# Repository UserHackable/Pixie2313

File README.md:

## Pixie 2313 / 4313

A very bare minimum breakout for an ATtiny2313 to provide the AVR ICSP programming header to the micro controller. 

## Pixie2313 

### Board dimensions

* (140000, 80000) original units
* (1.4000, 0.8000) inches
* (35.5600, 20.3200) mm

| Front | Back |
| --- | --- |
|  |  |

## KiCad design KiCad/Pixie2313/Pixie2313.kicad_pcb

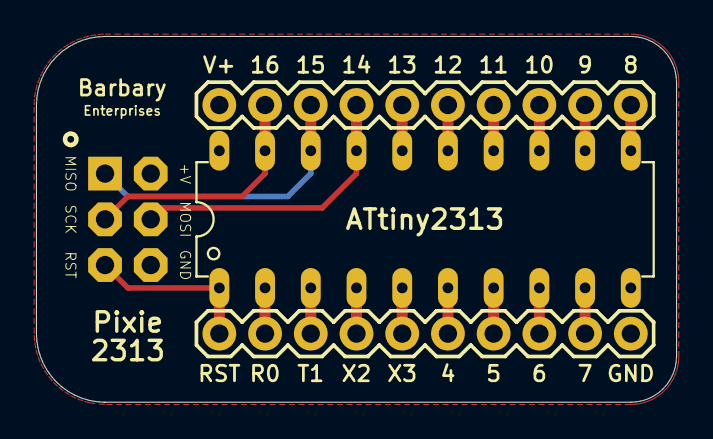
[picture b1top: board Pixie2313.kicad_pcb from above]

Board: 2 copper layers, 35.6 x 20.3 mm, 4 parts (0 on the bottom side), 20 nets.

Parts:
J1: AVR_SPI_PRG_6LABELED; 2X3-NS
JP1, JP2: M10"; 1X10
U1: DIL20

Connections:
0: JP1.9, U1.2
1: JP1.8, U1.3
2: JP1.5, U1.6
3: JP1.4, U1.7
4: JP1.3, U1.8
5: JP1.2, U1.9
6: JP2.10, U1.11
7: JP2.9, U1.12
8: JP2.8, U1.13
9: JP2.7, U1.14
10: JP2.6, U1.15
11: JP2.5, U1.16
12: J1.4, JP2.4, U1.17
13: J1.1, JP2.3, U1.18
14: J1.3, JP2.2, U1.19
GND: J1.6, JP1.1, U1.10
RST: J1.5, JP1.10, U1.1
VCC: J1.2, JP2.1, U1.20
X1: JP1.6, U1.5
X2: JP1.7, U1.4

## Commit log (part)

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2016-04-08 from Makefile
